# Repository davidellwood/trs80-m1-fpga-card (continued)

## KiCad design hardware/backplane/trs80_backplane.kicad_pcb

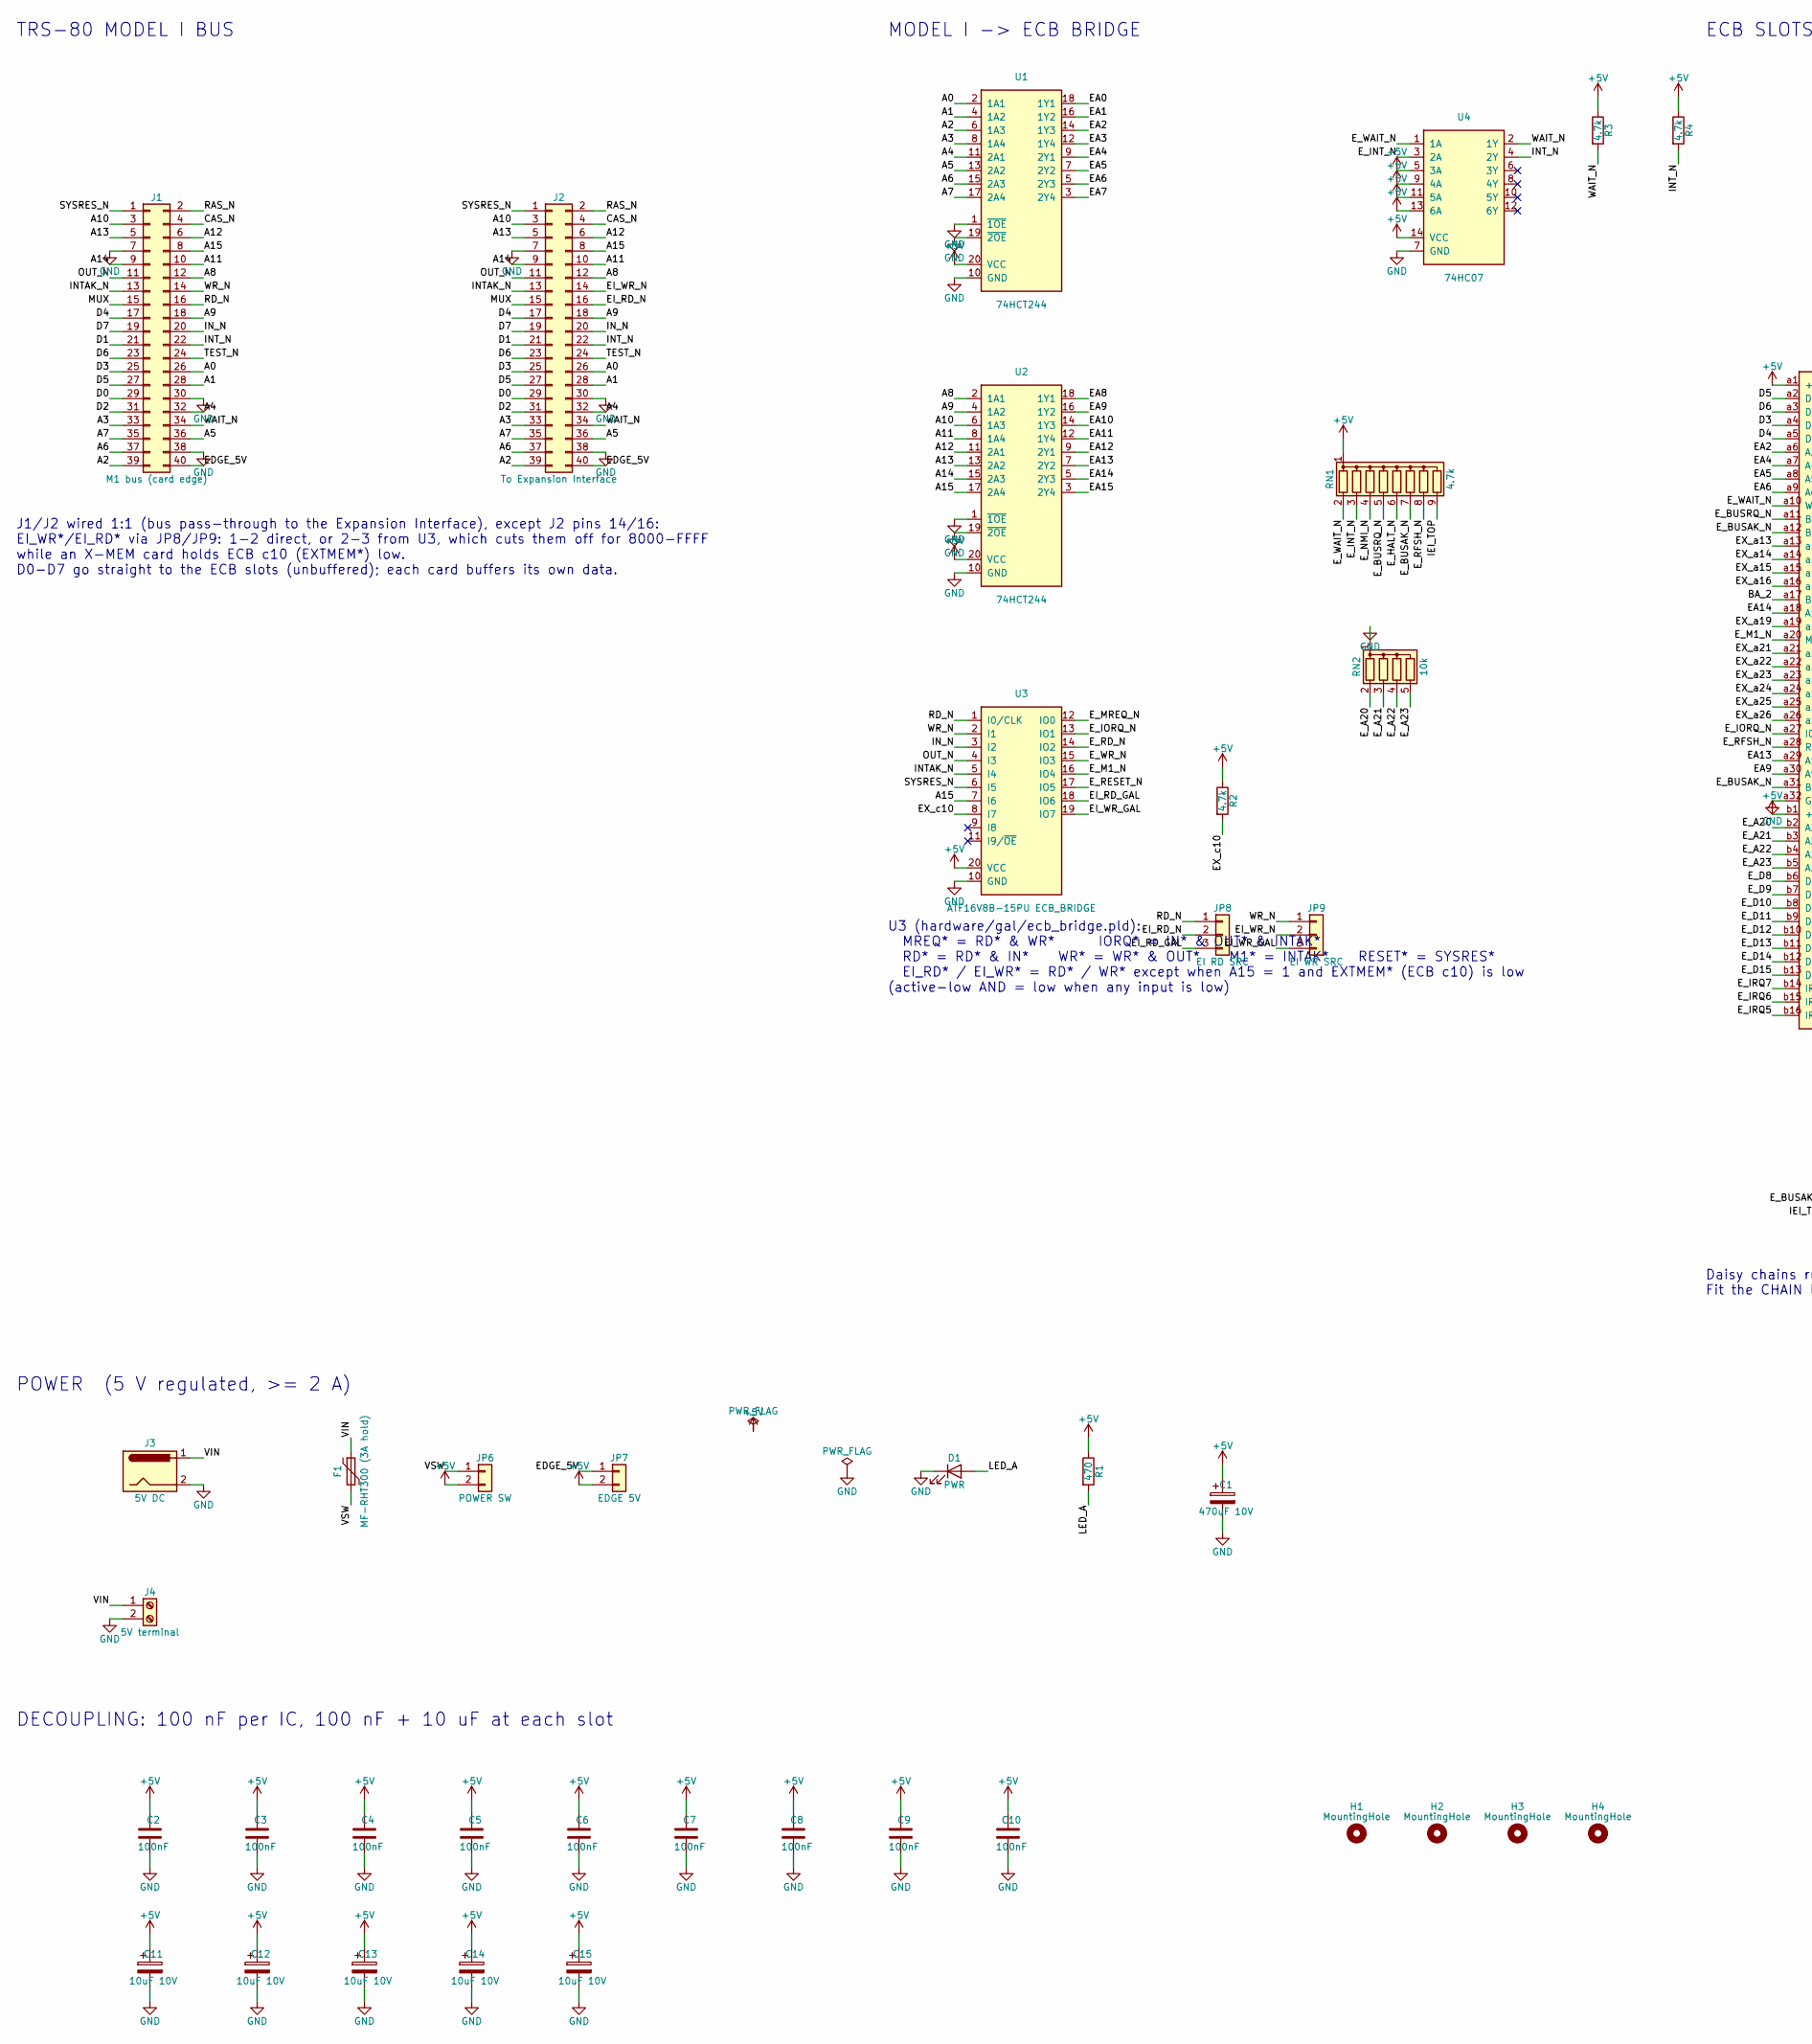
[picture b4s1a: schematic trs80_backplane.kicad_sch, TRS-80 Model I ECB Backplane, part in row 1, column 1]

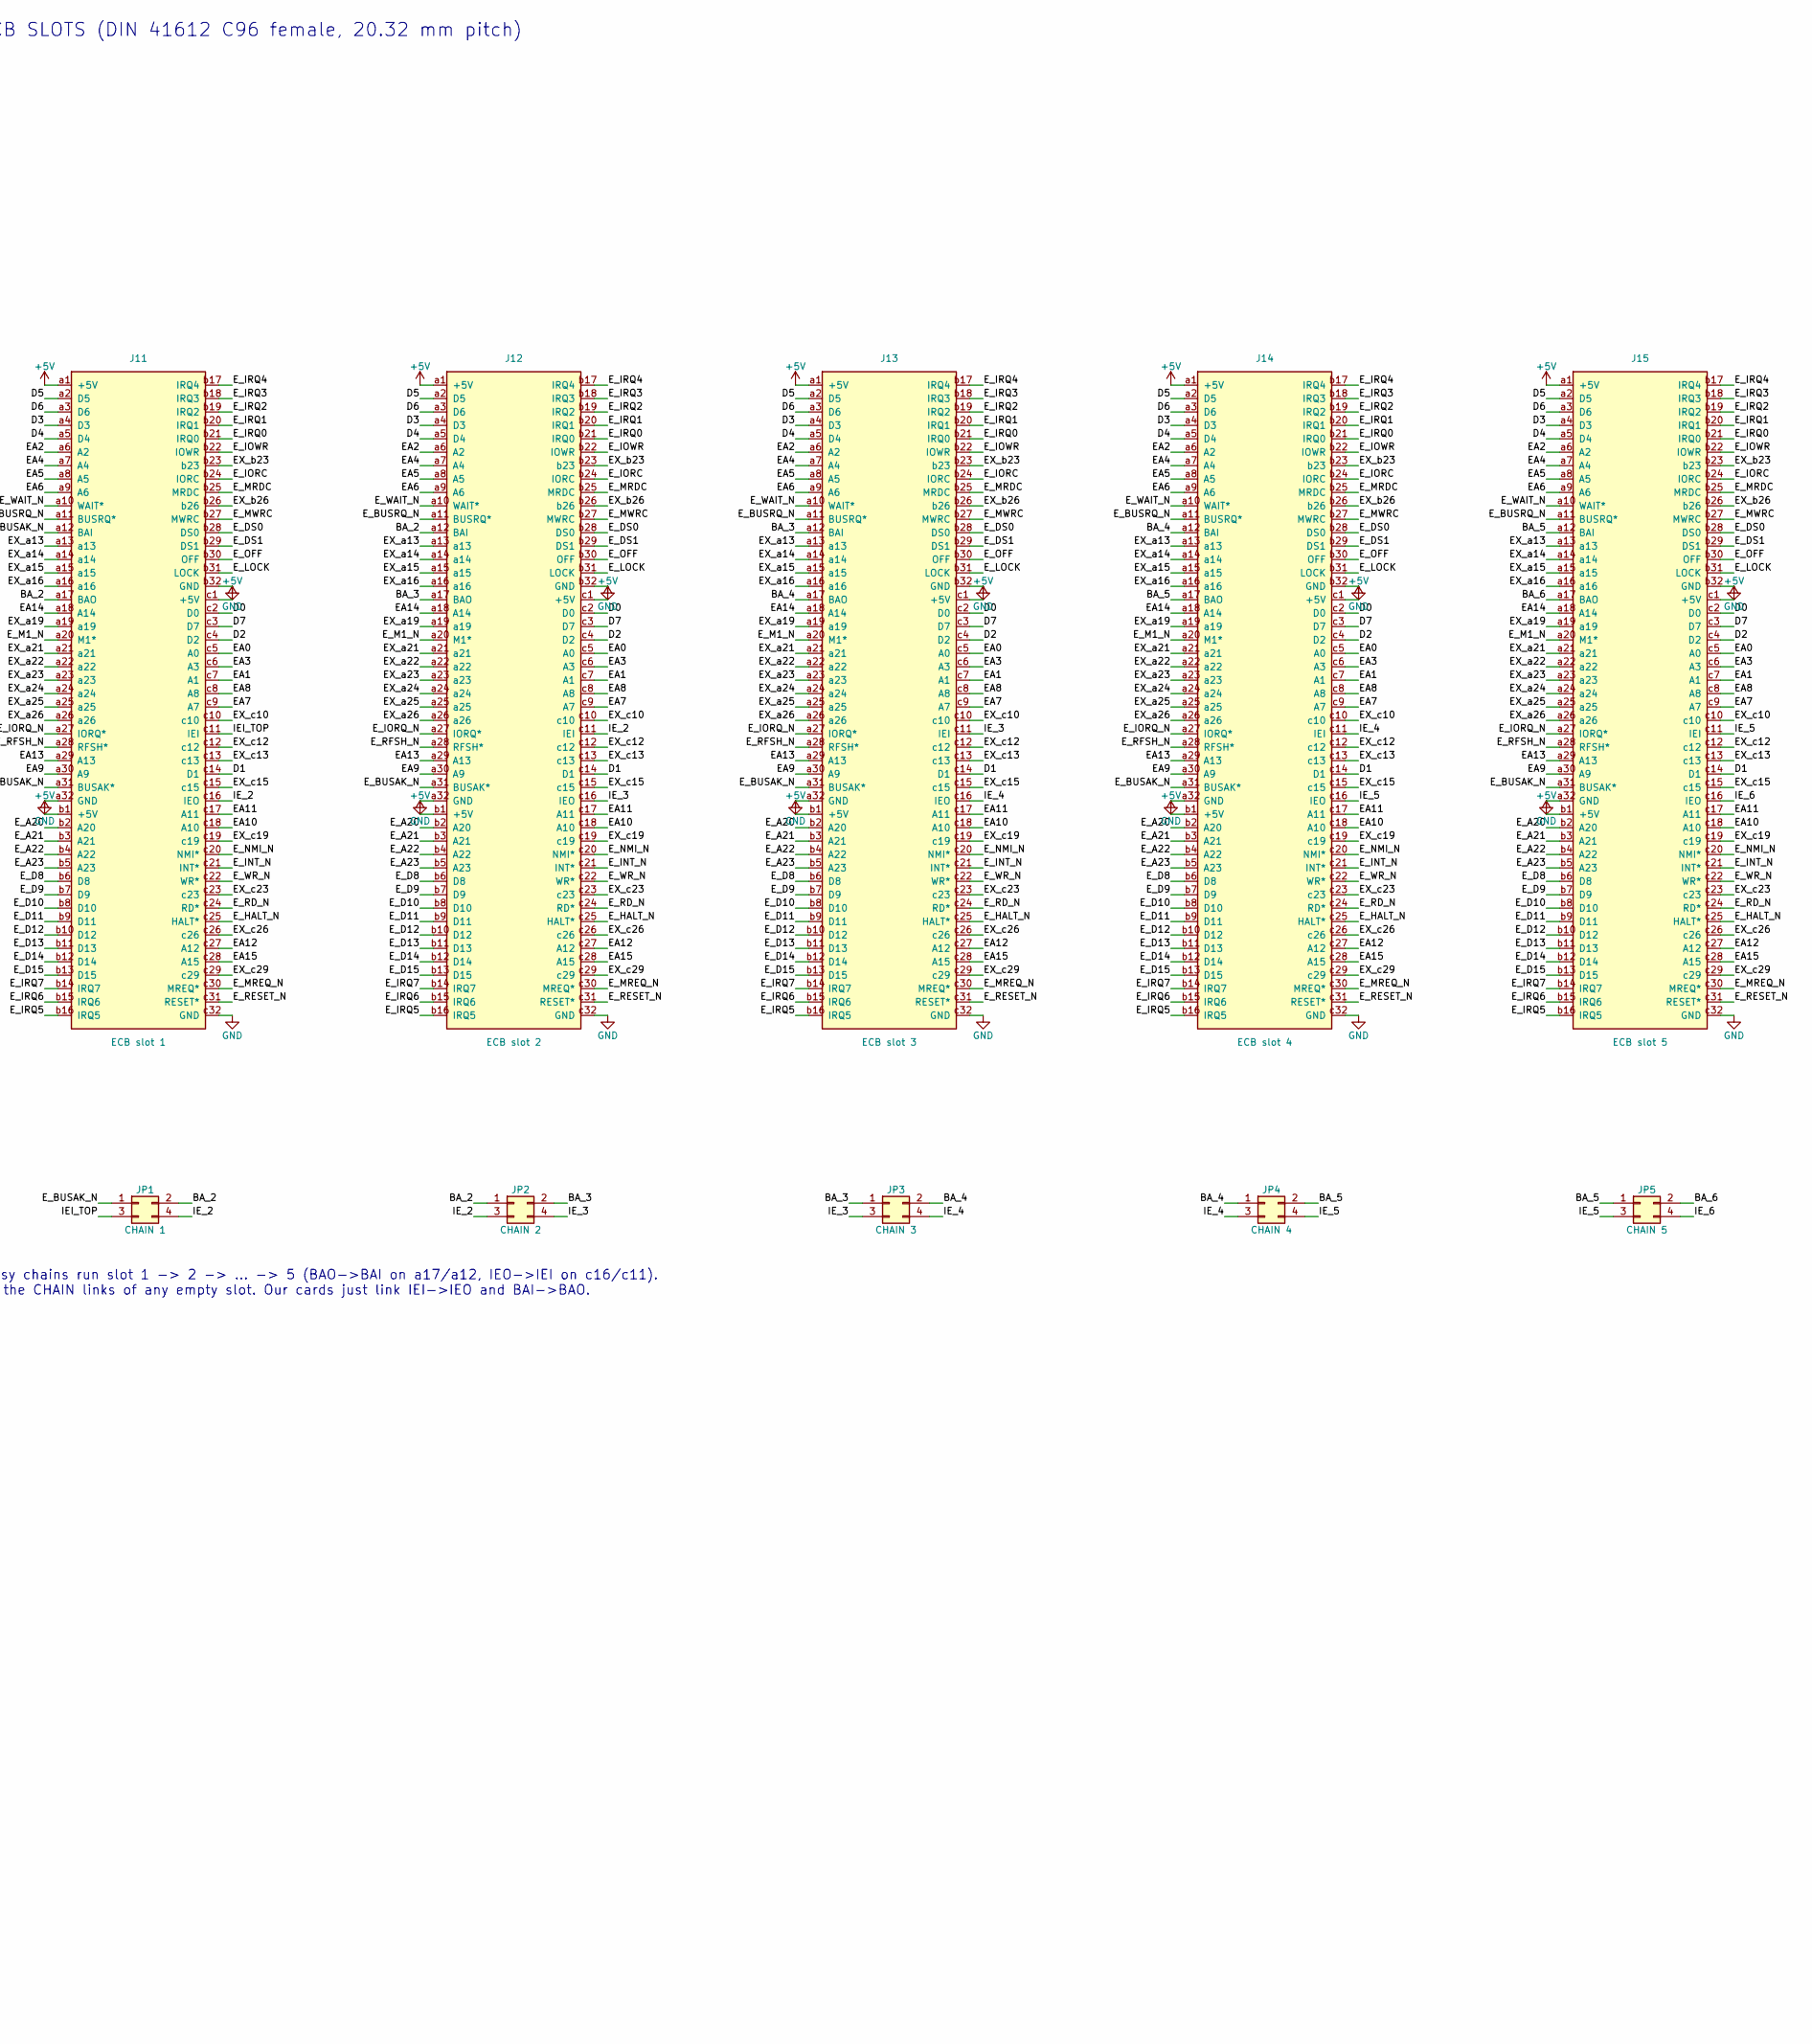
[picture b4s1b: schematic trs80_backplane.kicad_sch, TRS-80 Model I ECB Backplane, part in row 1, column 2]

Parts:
C1: 470uF 10V; CP_Radial_D10.0mm_P5.00mm
C2, C3, C4, C5, C6, C7, C8, C9, C10: 100nF; C_Disc_D5.0mm_W2.5mm_P5.00mm
C11, C12, C13, C14, C15: 10uF 10V; CP_Radial_D5.0mm_P2.00mm
D1: PWR; LED_D5.0mm
F1: MF-RHT300 (3A hold); Fuse_Bourns_MF-RHT300
H1, H2, H3, H4: MountingHole; MountingHole_3.2mm_M3
J1: M1 bus (card edge); TRS80_M1_Edge_40
J2: To Expansion Interface; IDC-Header_2x20_P2.54mm_Vertical
J3: 5V DC; BarrelJack_Horizontal
J4: 5V terminal; TerminalBlock_Phoenix_MKDS-1,5-2-5.08_1x02_P5.08mm_Horizont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
J11: ECB slot 1; DIN41612_C_3x32_Female_Vertical_THT
J12: ECB slot 2; DIN41612_C_3x32_Female_Vertical_THT
J13: ECB slot 3; DIN41612_C_3x32_Female_Vertical_THT
J14: ECB slot 4; DIN41612_C_3x32_Female_Vertical_THT
J15: ECB slot 5; DIN41612_C_3x32_Female_Vertical_THT
JP1: CHAIN 1; PinHeader_2x02_P2.54mm_Vertical
JP2: CHAIN 2; PinHeader_2x02_P2.54mm_Vertical
JP3: CHAIN 3; PinHeader_2x02_P2.54mm_Vertical
JP4: CHAIN 4; PinHeader_2x02_P2.54mm_Vertical
JP5: CHAIN 5; PinHeader_2x02_P2.54mm_Vertical
JP6: POWER SW; PinHeader_1x02_P2.54mm_Vertical
JP7: EDGE 5V; PinHeader_1x02_P2.54mm_Vertical
JP8: EI RD SRC; PinHeader_1x03_P2.54mm_Vertical
JP9: EI WR SRC; PinHeader_1x03_P2.54mm_Vertical
R1: 470; R_Axial_DIN0207_L6.3mm_D2.5mm_P10.16mm_Horizontal
R2, R3, R4: 4.7k; R_Axial_DIN0207_L6.3mm_D2.5mm_P10.16mm_Horizontal
RN1: 4.7k; R_Array_SIP9
RN2: 10k; R_Array_SIP5
U1, U2: 74HCT244; DIP-20_W7.62mm
U3: ATF16V8B-15PU ECB_BRIDGE; DIP-20_W7.62mm_Socket
U4: 74HC07; DIP-14_W7.62mm

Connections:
+5V: C1.1, C2.1, C3.1, C4.1, C5.1, C6.1, C7.1, C8.1, C9.1, C10.1, C11.1, C12.1, C13.1, C14.1, C15.1, J11.a1 (+5V), J11.b1 (+5V), J11.c1 (+5V), J12.a1 (+5V), J12.b1 (+5V), J12.c1 (+5V), J13.a1 (+5V), J13.b1 (+5V), J13.c1 (+5V), J14.a1 (+5V), J14.b1 (+5V), J14.c1 (+5V), J15.a1 (+5V), J15.b1 (+5V), J15.c1 (+5V), JP6.2, JP7.2, R1.1, R2.1, R3.1, R4.1, RN1.1 (common), U1.20 (VCC), U2.20 (VCC), U3.20 (VCC), U4.5 (3A), U4.9 (4A), U4.11 (5A), U4.13 (6A), U4.14 (VCC)
/A0: J1.26, J2.26, U1.2 (1A1)
/A1: J1.28, J2.28, U1.4 (1A2)
/A2: J1.39, J2.39, U1.6 (1A3)
/A3: J1.33, J2.33, U1.8 (1A4)
/A4: J1.32, J2.32, U1.11 (2A1)
/A5: J1.36, J2.36, U1.13 (2A2)
/A6: J1.37, J2.37, U1.15 (2A3)
/A7: J1.35, J2.35, U1.17 (2A4)
/A8: J1.12, J2.12, U2.2 (1A1)
/A9: J1.18, J2.18, U2.4 (1A2)
/A10: J1.3, J2.3, U2.6 (1A3)
/A11: J1.10, J2.10, U2.8 (1A4)
/A12: J1.6, J2.6, U2.11 (2A1)
/A13: J1.5, J2.5, U2.13 (2A2)
/A14: J1.9, J2.9, U2.15 (2A3)
/A15: J1.8, J2.8, U2.17 (2A4), U3.7 (I6)
/BA_2: J11.a17 (BAO), J12.a12 (BAI), JP1.2, JP2.1
/BA_3: J12.a17 (BAO), J13.a12 (BAI), JP2.2, JP3.1
/BA_4: J13.a17 (BAO), J14.a12 (BAI), JP3.2, JP4.1
/BA_5: J14.a17 (BAO), J15.a12 (BAI), JP4.2, JP5.1
/BA_6: J15.a17 (BAO), JP5.2
/CAS_N: J1.4, J2.4
/D0: J1.29, J2.29, J11.c2 (D0), J12.c2 (D0), J13.c2 (D0), J14.c2 (D0), J15.c2 (D0)
/D1: J1.21, J2.21, J11.c14 (D1), J12.c14 (D1), J13.c14 (D1), J14.c14 (D1), J15.c14 (D1)
/D2: J1.31, J2.31, J11.c4 (D2), J12.c4 (D2), J13.c4 (D2), J14.c4 (D2), J15.c4 (D2)
/D3: J1.25, J2.25, J11.a4 (D3), J12.a4 (D3), J13.a4 (D3), J14.a4 (D3), J15.a4 (D3)
/D4: J1.17, J2.17, J11.a5 (D4), J12.a5 (D4), J13.a5 (D4), J14.a5 (D4), J15.a5 (D4)
/D5: J1.27, J2.27, J11.a2 (D5), J12.a2 (D5), J13.a2 (D5), J14.a2 (D5), J15.a2 (D5)
/D6: J1.23, J2.23, J11.a3 (D6), J12.a3 (D6), J13.a3 (D6), J14.a3 (D6), J15.a3 (D6)
/D7: J1.19, J2.19, J11.c3 (D7), J12.c3 (D7), J13.c3 (D7), J14.c3 (D7), J15.c3 (D7)
/EA0: J11.c5 (A0), J12.c5 (A0), J13.c5 (A0), J14.c5 (A0), J15.c5 (A0), U1.18 (1Y1)
/EA1: J11.c7 (A1), J12.c7 (A1), J13.c7 (A1), J14.c7 (A1), J15.c7 (A1), U1.16 (1Y2)
/EA2: J11.a6 (A2), J12.a6 (A2), J13.a6 (A2), J14.a6 (A2), J15.a6 (A2), U1.14 (1Y3)
/EA3: J11.c6 (A3), J12.c6 (A3), J13.c6 (A3), J14.c6 (A3), J15.c6 (A3), U1.12 (1Y4)
/EA4: J11.a7 (A4), J12.a7 (A4), J13.a7 (A4), J14.a7 (A4), J15.a7 (A4), U1.9 (2Y1)
/EA5: J11.a8 (A5), J12.a8 (A5), J13.a8 (A5), J14.a8 (A5), J15.a8 (A5), U1.7 (2Y2)
/EA6: J11.a9 (A6), J12.a9 (A6), J13.a9 (A6), J14.a9 (A6), J15.a9 (A6), U1.5 (2Y3)
/EA7: J11.c9 (A7), J12.c9 (A7), J13.c9 (A7), J14.c9 (A7), J15.c9 (A7), U1.3 (2Y4)
/EA8: J11.c8 (A8), J12.c8 (A8), J13.c8 (A8), J14.c8 (A8), J15.c8 (A8), U2.18 (1Y1)
/EA9: J11.a30 (A9), J12.a30 (A9), J13.a30 (A9), J14.a30 (A9), J15.a30 (A9), U2.16 (1Y2)
/EA10: J11.c18 (A10), J12.c18 (A10), J13.c18 (A10), J14.c18 (A10), J15.c18 (A10), U2.14 (1Y3)
/EA11: J11.c17 (A11), J12.c17 (A11), J13.c17 (A11), J14.c17 (A11), J15.c17 (A11), U2.12 (1Y4)
/EA12: J11.c27 (A12), J12.c27 (A12), J13.c27 (A12), J14.c27 (A12), J15.c27 (A12), U2.9 (2Y1)
/EA13: J11.a29 (A13), J12.a29 (A13), J13.a29 (A13), J14.a29 (A13), J15.a29 (A13), U2.7 (2Y2)
/EA14: J11.a18 (A14), J12.a18 (A14), J13.a18 (A14), J14.a18 (A14), J15.a18 (A14), U2.5 (2Y3)
/EA15: J11.c28 (A15), J12.c28 (A15), J13.c28 (A15), J14.c28 (A15), J15.c28 (A15), U2.3 (2Y4)
/EDGE_5V: J1.40, J2.40, JP7.1
/EI_RD_GAL: JP8.3, U3.18 (IO6)
/EI_RD_N: J2.16, JP8.2
/EI_WR_GAL: JP9.3, U3.19 (IO7)
/EI_WR_N: J2.14, JP9.2
/EX_a13: J11.a13, J12.a13, J13.a13, J14.a13, J15.a13
/EX_a14: J11.a14, J12.a14, J13.a14, J14.a14, J15.a14
/EX_a15: J11.a15, J12.a15, J13.a15, J14.a15, J15.a15
/EX_a16: J11.a16, J12.a16, J13.a16, J14.a16, J15.a16
/EX_a19: J11.a19, J12.a19, J13.a19, J14.a19, J15.a19
/EX_a21: J11.a21, J12.a21, J13.a21, J14.a21, J15.a21
/EX_a22: J11.a22, J12.a22, J13.a22, J14.a22, J15.a22
/EX_a23: J11.a23, J12.a23, J13.a23, J14.a23, J15.a23
/EX_a24: J11.a24, J12.a24, J13.a24, J14.a24, J15.a24
/EX_a25: J11.a25, J12.a25, J13.a25, J14.a25, J15.a25
/EX_a26: J11.a26, J12.a26, J13.a26, J14.a26, J15.a26
/EX_b23: J11.b23, J12.b23, J13.b23, J14.b23, J15.b23
/EX_b26: J11.b26, J12.b26, J13.b26, J14.b26, J15.b26
/EX_c10: J11.c10, J12.c10, J13.c10, J14.c10, J15.c10, R2.2, U3.8 (I7)
/EX_c12: J11.c12, J12.c12, J13.c12, J14.c12, J15.c12
/EX_c13: J11.c13, J12.c13, J13.c13, J14.c13, J15.c13
/EX_c15: J11.c15, J12.c15, J13.c15, J14.c15, J15.c15
/EX_c19: J11.c19, J12.c19, J13.c19, J14.c19, J15.c19
/EX_c23: J11.c23, J12.c23, J13.c23, J14.c23, J15.c23
/EX_c26: J11.c26, J12.c26, J13.c26, J14.c26, J15.c26
/EX_c29: J11.c29, J12.c29, J13.c29, J14.c29, J15.c29
/E_A20: J11.b2 (A20), J12.b2 (A20), J13.b2 (A20), J14.b2 (A20), J15.b2 (A20), RN2.2 (R1)
/E_A21: J11.b3 (A21), J12.b3 (A21), J13.b3 (A21), J14.b3 (A21), J15.b3 (A21), RN2.3 (R2)
/E_A22: J11.b4 (A22), J12.b4 (A22), J13.b4 (A22), J14.b4 (A22), J15.b4 (A22), RN2.4 (R3)
/E_A23: J11.b5 (A23), J12.b5 (A23), J13.b5 (A23), J14.b5 (A23), J15.b5 (A23), RN2.5 (R4)
/E_BUSAK_N: J11.a12 (BAI), J11.a31 (BUSAK*), J12.a31 (BUSAK*), J13.a31 (BUSAK*), J14.a31 (BUSAK*), J15.a31 (BUSAK*), JP1.1, RN1.7 (R6)
/E_BUSRQ_N: J11.a11 (BUSRQ*), J12.a11 (BUSRQ*), J13.a11 (BUSRQ*), J14.a11 (BUSRQ*), J15.a11 (BUSRQ*), RN1.5 (R4)
/E_D8: J11.b6 (D8), J12.b6 (D8), J13.b6 (D8), J14.b6 (D8), J15.b6 (D8)
/E_D9: J11.b7 (D9), J12.b7 (D9), J13.b7 (D9), J14.b7 (D9), J15.b7 (D9)
/E_D10: J11.b8 (D10), J12.b8 (D10), J13.b8 (D10), J14.b8 (D10), J15.b8 (D10)
/E_D11: J11.b9 (D11), J12.b9 (D11), J13.b9 (D11), J14.b9 (D11), J15.b9 (D11)
/E_D12: J11.b10 (D12), J12.b10 (D12), J13.b10 (D12), J14.b10 (D12), J15.b10 (D12)
/E_D13: J11.b11 (D13), J12.b11 (D13), J13.b11 (D13), J14.b11 (D13), J15.b11 (D13)
/E_D14: J11.b12 (D14), J12.b12 (D14), J13.b12 (D14), J14.b12 (D14), J15.b12 (D14)
/E_D15: J11.b13 (D15), J12.b13 (D15), J13.b13 (D15), J14.b13 (D15), J15.b13 (D15)
/E_DS0: J11.b28 (DS0), J12.b28 (DS0), J13.b28 (DS0), J14.b28 (DS0), J15.b28 (DS0)
/E_DS1: J11.b29 (DS1), J12.b29 (DS1), J13.b29 (DS1), J14.b29 (DS1), J15.b29 (DS1)
/E_HALT_N: J11.c25 (HALT*), J12.c25 (HALT*), J13.c25 (HALT*), J14.c25 (HALT*), J15.c25 (HALT*), RN1.6 (R5)
/E_INT_N: J11.c21 (INT*), J12.c21 (INT*), J13.c21 (INT*), J14.c21 (INT*), J15.c21 (INT*), RN1.3 (R2), U4.3 (2A)
/E_IORC: J11.b24 (IORC), J12.b24 (IORC), J13.b24 (IORC), J14.b24 (IORC), J15.b24 (IORC)
/E_IORQ_N: J11.a27 (IORQ*), J12.a27 (IORQ*), J13.a27 (IORQ*), J14.a27 (IORQ*), J15.a27 (IORQ*), U3.13 (IO1)
/E_IOWR: J11.b22 (IOWR), J12.b22 (IOWR), J13.b22 (IOWR), J14.b22 (IOWR), J15.b22 (IOWR)
/E_IRQ0: J11.b21 (IRQ0), J12.b21 (IRQ0), J13.b21 (IRQ0), J14.b21 (IRQ0), J15.b21 (IRQ0)
/E_IRQ1: J11.b20 (IRQ1), J12.b20 (IRQ1), J13.b20 (IRQ1), J14.b20 (IRQ1), J15.b20 (IRQ1)
/E_IRQ2: J11.b19 (IRQ2), J12.b19 (IRQ2), J13.b19 (IRQ2), J14.b19 (IRQ2), J15.b19 (IRQ2)
/E_IRQ3: J11.b18 (IRQ3), J12.b18 (IRQ3), J13.b18 (IRQ3), J14.b18 (IRQ3), J15.b18 (IRQ3)
/E_IRQ4: J11.b17 (IRQ4), J12.b17 (IRQ4), J13.b17 (IRQ4), J14.b17 (IRQ4), J15.b17 (IRQ4)
/E_IRQ5: J11.b16 (IRQ5), J12.b16 (IRQ5), J13.b16 (IRQ5), J14.b16 (IRQ5), J15.b16 (IRQ5)
/E_IRQ6: J11.b15 (IRQ6), J12.b15 (IRQ6), J13.b15 (IRQ6), J14.b15 (IRQ6), J15.b15 (IRQ6)
/E_IRQ7: J11.b14 (IRQ7), J12.b14 (IRQ7), J13.b14 (IRQ7), J14.b14 (IRQ7), J15.b14 (IRQ7)
/E_LOCK: J11.b31 (LOCK), J12.b31 (LOCK), J13.b31 (LOCK), J14.b31 (LOCK), J15.b31 (LOCK)
/E_M1_N: J11.a20 (M1*), J12.a20 (M1*), J13.a20 (M1*), J14.a20 (M1*), J15.a20 (M1*), U3.16 (IO4)
/E_MRDC: J11.b25 (MRDC), J12.b25 (MRDC), J13.b25 (MRDC), J14.b25 (MRDC), J15.b25 (MRDC)
/E_MREQ_N: J11.c30 (MREQ*), J12.c30 (MREQ*), J13.c30 (MREQ*), J14.c30 (MREQ*), J15.c30 (MREQ*), U3.12 (IO0)
/E_MWRC: J11.b27 (MWRC), J12.b27 (MWRC), J13.b27 (MWRC), J14.b27 (MWRC), J15.b27 (MWRC)
/E_NMI_N: J11.c20 (NMI*), J12.c20 (NMI*), J13.c20 (NMI*), J14.c20 (NMI*), J15.c20 (NMI*), RN1.4 (R3)
/E_OFF: J11.b30 (OFF), J12.b30 (OFF), J13.b30 (OFF), J14.b30 (OFF), J15.b30 (OFF)
/E_RD_N: J11.c24 (RD*), J12.c24 (RD*), J13.c24 (RD*), J14.c24 (RD*), J15.c24 (RD*), U3.14 (IO2)
/E_RESET_N: J11.c31 (RESET*), J12.c31 (RESET*), J13.c31 (RESET*), J14.c31 (RESET*), J15.c31 (RESET*), U3.17 (IO5)
/E_RFSH_N: J11.a28 (RFSH*), J12.a28 (RFSH*), J13.a28 (RFSH*), J14.a28 (RFSH*), J15.a28 (RFSH*), RN1.8 (R7)
/E_WAIT_N: J11.a10 (WAIT*), J12.a10 (WAIT*), J13.a10 (WAIT*), J14.a10 (WAIT*), J15.a10 (WAIT*), RN1.2 (R1), U4.1 (1A)
/E_WR_N: J11.c22 (WR*), J12.c22 (WR*), J13.c22 (WR*), J14.c22 (WR*), J15.c22 (WR*), U3.15 (IO3)
/IEI_TOP: J11.c11 (IEI), JP1.3, RN1.9 (R8)
/IE_2: J11.c16 (IEO), J12.c11 (IEI), JP1.4, JP2.3
/IE_3: J12.c16 (IEO), J13.c11 (IEI), JP2.4, JP3.3
/IE_4: J13.c16 (IEO), J14.c11 (IEI), JP3.4, JP4.3
/IE_5: J14.c16 (IEO), J15.c11 (IEI), JP4.4, JP5.3
/IE_6: J15.c16 (IEO), JP5.4
/INTAK_N: J1.13, J2.13, U3.5 (I4)
/INT_N: J1.22, J2.22, R4.2, U4.4 (2Y)
/IN_N: J1.20, J2.20, U3.3 (I2)
/LED_A: D1.2 (A), R1.2
/MUX: J1.15, J2.15
/OUT_N: J1.11, J2.11, U3.4 (I3)
/RAS_N: J1.2, J2.2
/RD_N: J1.16, JP8.1, U3.1 (I0/CLK)
/SYSRES_N: J1.1, J2.1, U3.6 (I5)
/TEST_N: J1.24, J2.24
/VIN: F1.1, J3.1, J4.1
/VSW: F1.2, JP6.1
/WAIT_N: J1.34, J2.34, R3.2, U4.2 (1Y)
/WR_N: J1.14, JP9.1, U3.2 (I1)
GND: C1.2, C2.2, C3.2, C4.2, C5.2, C6.2, C7.2, C8.2, C9.2, C10.2, C11.2, C12.2, C13.2, C14.2, C15.2, D1.1 (K), J1.7, J1.30, J1.38, J2.7, J2.30, J2.38, J3.2, J4.2, J11.a32 (GND), J11.b32 (GND), J11.c32 (GND), J12.a32 (GND), J12.b32 (GND), J12.c32 (GND), J13.a32 (GND), J13.b32 (GND), J13.c32 (GND), J14.a32 (GND), J14.b32 (GND), J14.c32 (GND), J15.a32 (GND), J15.b32 (GND), J15.c32 (GND), RN2.1 (common), U1.1 (~1OE), U1.10 (GND), U1.19 (~2OE), U2.1 (~1OE), U2.10 (GND), U2.19 (~2OE), U3.10 (GND), U4.7 (GND)

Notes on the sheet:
TRS-80 MODEL I BUS
J1/J2 wired 1:1 (bus pass-through to the Expansion Interface), except J2 pins 14/16: EI_WR*/EI_RD* via JP8/JP9: 1-2 direct, or 2-3 from U3, which cuts them off for 8000-FFFF while an X-MEM card holds ECB c10 (EXTMEM*) low. D0-D7 go straight to the ECB slots (unbuffered); each card buffers its own d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
MODEL I -> ECB BRIDGE
U3 (hardware/gal/ecb_bridge.pld): MREQ* = RD* & WR* IORQ* = IN* & OUT* & INTAK* RD* = RD* & IN* WR* = WR* & OUT* M1* = INTAK* RESET* = SYSRES* EI_RD* / EI_WR* = RD* / WR* except when A15 = 1 and EXTMEM* (ECB c10) is low (active-low AND = low when any input is low)
ECB SLOTS (DIN 41612 C96 female, 20.32 mm pitch)
Daisy chains run slot 1 -> 2 -> ... -> 5 (BAO->BAI on a17/a12, IEO->IEI on c16/c11). Fit the CHAIN links of any empty slot. Our cards just link IEI->IEO and BAI->BAO.
POWER (5 V regulated, >= 2 A)
DECOUPLING: 100 nF per IC, 100 nF + 10 uF at each slot

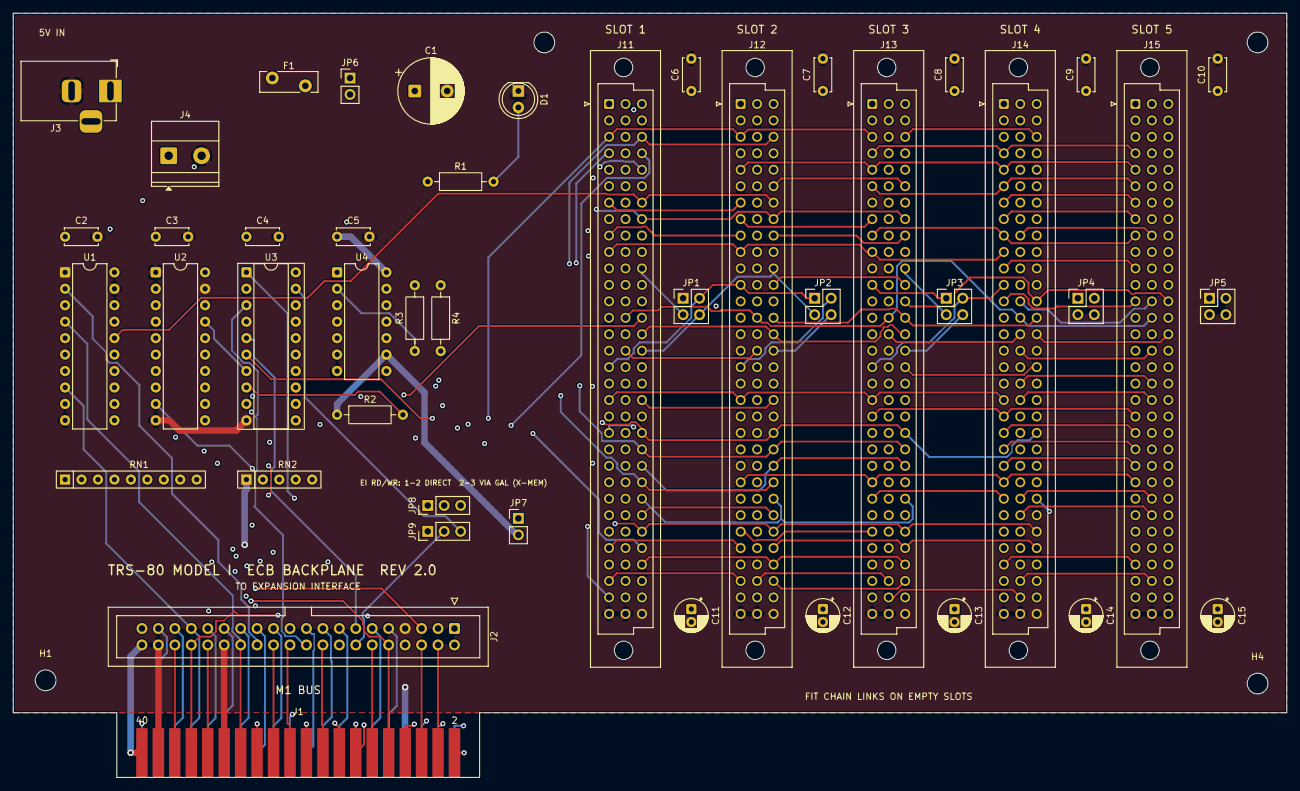
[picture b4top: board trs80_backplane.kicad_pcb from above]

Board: 4 copper layers, 196.6 x 118.0 mm, 49 parts (0 on the bottom side), 135 nets.

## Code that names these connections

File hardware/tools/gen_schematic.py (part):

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       "9": "OUT_N", "11": "PORT_ALT_N", "12": "IORD", "13": "IOWR", "14": "DP_CE_N", "15": "MEMQ",
       "16": "ACT_LED_N", "17": "NC", "18": "NC", "19": "NC", "20": "+5V", "10": "GND"})
text("U4: DP_CE_N low for RD/WR in 0x3000-0x37DF (0x37FF with FULL jumper).\n"
     "     Qualified by MEMQ (no I/O cycle). Pin 22 spare.\n"
     "U5: IORD / IOWR high for IN / OUT on ports 0x50-0x53 (0x70-0x73 with ALT jumper).\n"
     "     A1:A0 go to the FPGA: 0 APU data, 1 APU cmd/status, 2 GFX data, 3 GFX cmd/status.",
     190.5, 185.42)
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# ---- 5V -> 3.3V ----
text("5V -> 3.3V", 535.94, 40.64, 2.5)
place("U6", LIB + ":CD74HC4050", "CD74HC4050E", "Package_DIP:DIP-16_W7.62mm", 558.8, 76.2,
      {"3": "SYSRES_N", "2": "SYSRES_3V3_N", "5": "A1", "4": "PA1_3V3",
       "7": "IORD", "6": "IORD_3V3", "9": "IOWR", "10": "IOWR_3V3",
       "11": "A0", "12": "PA0_3V3", "14": "BUSY_R_N", "15": "R_BUSY_3V3_N",
       "1": "+3V3", "8": "GND", "13": "NC", "16": "NC"})

# ---- FPGA ----
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        "5": "RA0", "6": "RA1", "7": "RA2", "8": "RA3", "9": "RA4", "10": "RA5", "11": "RA6",
        "12": "RA7", "13": "RA8", "14": "RA9", "15": "RA10",
        "16": "FD0", "17": "FD1", "18": "FD2", "19": "FD3", "20": "FD4", "21": "FD5", "22": "FD6",
        "23": "GPIO_P68", "24": "GPIO_P69",
        "25": "+3V3", "26": "GND", "27": "FD7", "28": "R_BUSY_3V3_N", "29": "IORD_3V3",
        "30": "IOWR_3V3", "31": "TANG_5V", "32": "PORT_OE_N", "33": "R_CE_N", "34": "R_RW_N",
        "35": "GPIO_P73", "36": "WAIT_DRV", "37": "INT_DRV", "38": "PA0_3V3", "39": "PA1_3V3",
        "40": "GPIO_P79", "41": "GPIO_P80", "42": "GPIO_P81", "43": "GPIO_P82", "44": "GPIO_P83",
        "45": "GPIO_P84", "46": "GPIO_P85", "47": "GPIO_P86", "48": "SYSRES_3V3_N"}
place("U7", LIB + ":TangNano9K", "Tang Nano 9K", LIB + ":TangNano9K_DIP48_W22.86mm", 685.8, 99.06, tang)
text("Header pins 1-4 (P36-P39) are used by the module's own TF card slot.\n"
     "P79-P86 are the 1.8V bank: only to J4, never to 3.3V/5V logic.\n"
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place("D2", "Device:D_Schottky", "1N5819", FP_DO41, 134.62, 304.8, {"1": "TANG_5V", "2": "+5V"},
      "Feeds the Tang Nano 5V pin; blocks back-feed when the module is on USB")
place("JP5", "Connector_Generic:Conn_01x02", "EDGE 5V", FP_JP, 175.26, 304.8,
      {"1": "EDGE_5V", "2": "+5V"}, "Leave open unless the bus pin 40 supply is known good")
power("+5V", 210.82, 297.18, flag=True)
power("GND", 236.22, 304.8, flag=True)
place("D4", "Device:LED", "ACT (green)", FP_LED, 299.72, 304.8, {"1": "ACT_LED_N", "2": "ACT_A"})
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text("FPGA EXPANSION HEADER", 238.76, 391.16, 2.5)
place("J4", "Connector_Generic:Conn_02x08_Odd_Even", "FPGA spare I/O",
      "Connector_PinHeader_2.54mm:PinHeader_2x08_P2.54mm_Vertical", 266.7, 421.64,
      {"1": "+3V3", "2": "GND", "3": "GPIO_P68", "4": "GPIO_P69", "5": "GPIO_P73", "6": "GND",
       "7": "GPIO_P79", "8": "GPIO_P80", "9": "GPIO_P81", "10": "GPIO_P82", "11": "GPIO_P83",
       "12": "GPIO_P84", "13": "GPIO_P85", "14": "GPIO_P86", "15": "GND", "16": "GND"},
      "Pins 7-14 are 1.8V I/O")
for i in range(4):
    place("H%d" % (i + 1), "Mechanical:MountingHole", "MountingHole", "MountingHole:MountingHole_3.2mm_M3",
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
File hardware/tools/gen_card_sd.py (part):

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See docs/rev2-architecture.md and firmware/sdcard/. Writes hardware/card-sd/.

Bus interface: U2 GAL decodes C0-CF and holds WAIT* until the Pico raises ACK.
Data: U1 74HCT245 (5 V) <-> XD <-> 2N7000 shifters <-> PD0-7 on Pico GP0-7.
Address A0-A3 and the strobes reach the Pico through CD74HC4050 buffers.
One-shot bootstrap: don't re-run after hand edits in KiCad.
"""
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
p.text("5V -> 3.3V", 279.4, 30.48, 2.5)
p.place("U3", LIB + ":CD74HC4050", "CD74HC4050E", "Package_DIP:DIP-16_W7.62mm", 304.8, 66.04,
        {"3": "A0", "2": "PA0", "5": "A1", "4": "PA1", "7": "A2", "6": "PA2", "9": "A3", "10": "PA3",
         "11": "SELRD", "12": "SELRD_3V3", "14": "SELWR", "15": "SELWR_3V3",
         "1": "+3V3", "8": "GND", "13": "NC", "16": "NC"})
p.place("U4", LIB + ":CD74HC4050", "CD74HC4050E", "Package_DIP:DIP-16_W7.62mm", 304.8, 116.84,
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
# ---------------------------------------------------------------- Pico
p.text("RASPBERRY PI PICO  (socketed)", 381, 30.48, 2.5)
pico = {"1": "PD0", "2": "PD1", "4": "PD2", "5": "PD3", "6": "PD4", "7": "PD5", "9": "PD6", "10": "PD7",
        "11": "PA0", "12": "PA1", "14": "PA2", "15": "PA3", "16": "SELRD_3V3", "17": "SELWR_3V3",
        "19": "ACK", "20": "RESET_3V3_N",
        "21": "SD_MISO", "22": "SD_CS", "24": "SD_SCK", "25": "SD_MOSI", "26": "SD_CD", "27": "LED_ACT",
        "29": "GP22", "31": "I2C_SDA", "32": "I2C_SCL", "34": "GP28",
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        "Pico VSYS from +5V; blocks back-feed when the Pico is on USB")
p.place("R6", "Device:R", "10k", FP_R, 444.5, 152.4, {"1": "+3V3", "2": "ACK"},
        "ACK pull-up: no WAIT when the Pico is absent or not yet running")
p.text("GP0-7 PD0-7 (data)   GP8-11 PA0-3 (A0-A3)   GP12 SELRD   GP13 SELWR\n"
       "GP14 ACK   GP15 RESET_N   GP16-19 SPI0 to SD (MISO, CS, SCK, MOSI)\n"
       "GP20 SD card detect   GP21 ACT LED   GP26/27 I2C1 to the DS1307\n"
       "GP22, GP28 spare (J3).  Pico 3V3 OUT powers the card's 3.3 V logic.",
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
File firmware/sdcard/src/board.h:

/* Pico pin use on the ECB SD card (hardware/card-sd). */
#ifndef BOARD_H
#define BOARD_H

#define PIN_PD0      0    /* GP0-GP7: data PD0-PD7, via 2N7000 shifters to XD (U1 245 to ECB D0-D7) */
#define PIN_PA0      8    /* GP8-GP11: ECB A0-A3 via U3 (CD74HC4050) */
#define PIN_SELRD    12   /* GAL: IN from C0-CF in progress (active high) */
#define PIN_SELWR    13   /* GAL: OUT to C0-CF in progress (active high) */
#define PIN_ACK      14   /* to GAL: high releases WAIT* (10k pull-up on the card) */
#define PIN_RESET    15   /* ECB RESET* via U4 (active low) */

#define SD_SPI       spi0
#define PIN_SD_MISO  16
#define PIN_SD_CS    17
#define PIN_SD_SCK   18
#define PIN_SD_MOSI  19
#define PIN_SD_CD    20   /* card detect from the module, 10k pull-up; see USE_CARD_DETECT */
#define PIN_LED      21   /* ACT LED, active high */

#define RTC_I2C      i2c1
#define PIN_SDA      26
#define PIN_SCL      27

/* Card-detect switch: 0 = ignore it and probe the card instead (works with any module).
   Set to 1 and CD_INSERTED_LEVEL to the module's level with a card fitted to use it. */
#define USE_CARD_DETECT   0
#define CD_INSERTED_LEVEL 1

#define MASK_PD   (0xFFu << PIN_PD0)
#define MASK_SEL  ((1u << PIN_SELRD) | (1u << PIN_SELWR))

#endif

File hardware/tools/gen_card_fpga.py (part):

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# ---------------------------------------------------------------- 5V -> 3.3V
p.text("5V -> 3.3V", 505.46, 30.48, 2.5)
p.place("U6", LIB + ":CD74HC4050", "CD74HC4050E", "Package_DIP:DIP-16_W7.62mm", 528.32, 66.04,
        {"3": "RESET_N", "2": "RESET_3V3_N", "5": "A1", "4": "PA1_3V3",
         "7": "IORD", "6": "IORD_3V3", "9": "IOWR", "10": "IOWR_3V3",
         "11": "A0", "12": "PA0_3V3", "14": "BUSY_R_N", "15": "R_BUSY_3V3_N",
         "1": "+3V3", "8": "GND", "13": "NC", "16": "NC"})

# ---------------------------------------------------------------- FPGA
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        "15": "R_CE_N", "16": "R_RW_N", "17": "PORT_OE_N", "20": "RESET_3V3_N", "19": "R_BUSY_3V3_N",
        "18": "IORD_3V3",
        "80": "FD0", "42": "FD1", "41": "FD2", "56": "FD3", "54": "FD4", "48": "FD5", "55": "FD6", "49": "FD7",
        "86": "WAIT_DRV", "72": "INT_DRV", "71": "IOWR_3V3", "53": "PA0_3V3", "52": "PA1_3V3",
        "75": "NC", "76": "NC", "51": "NC", "79": "NC",
        "3V3": "+3V3", "GND": "GND", "5V": "TANG_5V"}
tang = {}
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
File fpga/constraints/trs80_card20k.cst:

// Tang Nano 20K (GW2AR-LV18QN88C8/I7) pin constraints for the rev 2 ECB FPGA card.
// Numbers are GW2AR-18 QN88 package pins; header positions are in
// hardware/tools/gen_card_fpga.py (TANG_L / TANG_R) and docs/rev2-architecture.md.
// All header banks are 3.3 V.

// ---- on-board ----
IO_LOC  "clk27" 4;
IO_PORT "clk27" IO_TYPE=LVCMOS33 PULL_MODE=UP;
IO_LOC  "pa_en" 51;
IO_PORT "pa_en" IO_TYPE=LVCMOS33 DRIVE=8;
IO_LOC  "ws2812" 79;
IO_PORT "ws2812" IO_TYPE=LVCMOS33 DRIVE=8;

// ---- IDT7132 right-port address (left header) ----
IO_LOC "ra[0]" 73;
IO_LOC "ra[1]" 74;
IO_LOC "ra[2]" 85;
IO_LOC "ra[3]" 77;
IO_LOC "ra[4]" 27;
IO_LOC "ra[5]" 28;
IO_LOC "ra[6]" 25;
IO_LOC "ra[7]" 26;
IO_LOC "ra[8]" 29;
IO_LOC "ra[9]" 30;
IO_LOC "ra[10]" 31;
IO_PORT "ra[0]" IO_TYPE=LVCMOS33 DRIVE=8;
IO_PORT "ra[1]" IO_TYPE=LVCMOS33 DRIVE=8;
IO_PORT "ra[2]" IO_TYPE=LVCMOS33 DRIVE=8;
IO_PORT "ra[3]" IO_TYPE=LVCMOS33 DRIVE=8;
IO_PORT "ra[4]" IO_TYPE=LVCMOS33 DRIVE=8;
IO_PORT "ra[5]" IO_TYPE=LVCMOS33 DRIVE=8;
IO_PORT "ra[6]" IO_TYPE=LVCMOS33 DRIVE=8;
IO_PORT "ra[7]" IO_TYPE=LVCMOS33 DRIVE=8;
IO_PORT "ra[8]" IO_TYPE=LVCMOS33 DRIVE=8;
IO_PORT "ra[9]" IO_TYPE=LVCMOS33 DRIVE=8;
IO_PORT "ra[10]" IO_TYPE=LVCMOS33 DRIVE=8;

// ---- DPRAM / port control (left header, on the module LED pins) ----
IO_LOC  "r_ce_n" 15;        // LED0
IO_LOC  "r_rw_n" 16;        // LED1
IO_LOC  "port_oe_n" 17;     // LED2
IO_PORT "r_ce_n" IO_TYPE=LVCMOS33 DRIVE=8;
IO_PORT "r_rw_n" IO_TYPE=LVCMOS33 DRIVE=8;
IO_PORT "port_oe_n" IO_TYPE=LVCMOS33 DRIVE=8;

// ---- inputs from U6 (CD74HC4050, push-pull) ----
IO_LOC  "iord" 18;          // LED3
IO_LOC  "r_busy_n" 19;      // LED4
IO_LOC  "reset_n" 20;       // LED5
IO_LOC  "iowr" 71;
IO_LOC  "pa[0]" 53;
IO_LOC  "pa[1]" 52;
IO_PORT "iord" IO_TYPE=LVCMOS33 PULL_MODE=NONE;
IO_PORT "r_busy_n" IO_TYPE=LVCMOS33 PULL_MODE=NONE;
IO_PORT "reset_n" IO_TYPE=LVCMOS33 PULL_MODE=NONE;
IO_PORT "iowr" IO_TYPE=LVCMOS33 PULL_MODE=NONE;
IO_PORT "pa[0]" IO_TYPE=LVCMOS33 PULL_MODE=NONE;
IO_PORT "pa[1]" IO_TYPE=LVCMOS33 PULL_MODE=NONE;

// ---- shared data bus FD0-FD7 (right header; 4.7k pull-ups on the card) ----
IO_LOC "fd[0]" 80;
IO_LOC "fd[1]" 42;
IO_LOC "fd[2]" 41;
IO_LOC "fd[3]" 56;
IO_LOC "fd[4]" 54;
IO_LOC "fd[5]" 48;
IO_LOC "fd[6]" 55;
IO_LOC "fd[7]" 49;
IO_PORT "fd[0]" IO_TYPE=LVCMOS33 PULL_MODE=NONE DRIVE=8;
IO_PORT "fd[1]" IO_TYPE=LVCMOS33 PULL_MODE=NONE DRIVE=8;
IO_PORT "fd[2]" IO_TYPE=LVCMOS33 PULL_MODE=NONE DRIVE=8;
IO_PORT "fd[3]" IO_TYPE=LVCMOS33 PULL_MODE=NONE DRIVE=8;
IO_PORT "fd[4]" IO_TYPE=LVCMOS33 PULL_MODE=NONE DRIVE=8;
IO_PORT "fd[5]" IO_TYPE=LVCMOS33 PULL_MODE=NONE DRIVE=8;
IO_PORT "fd[6]" IO_TYPE=LVCMOS33 PULL_MODE=NONE DRIVE=8;
IO_PORT "fd[7]" IO_TYPE=LVCMOS33 PULL_MODE=NONE DRIVE=8;

// ---- open-drain gate drivers (10k pull-downs on the card) ----
IO_LOC  "wait_drv" 86;
IO_LOC  "int_drv" 72;
IO_PORT "wait_drv" IO_TYPE=LVCMOS33 DRIVE=8;
IO_PORT "int_drv" IO_TYPE=LVCMOS33 DRIVE=8;
